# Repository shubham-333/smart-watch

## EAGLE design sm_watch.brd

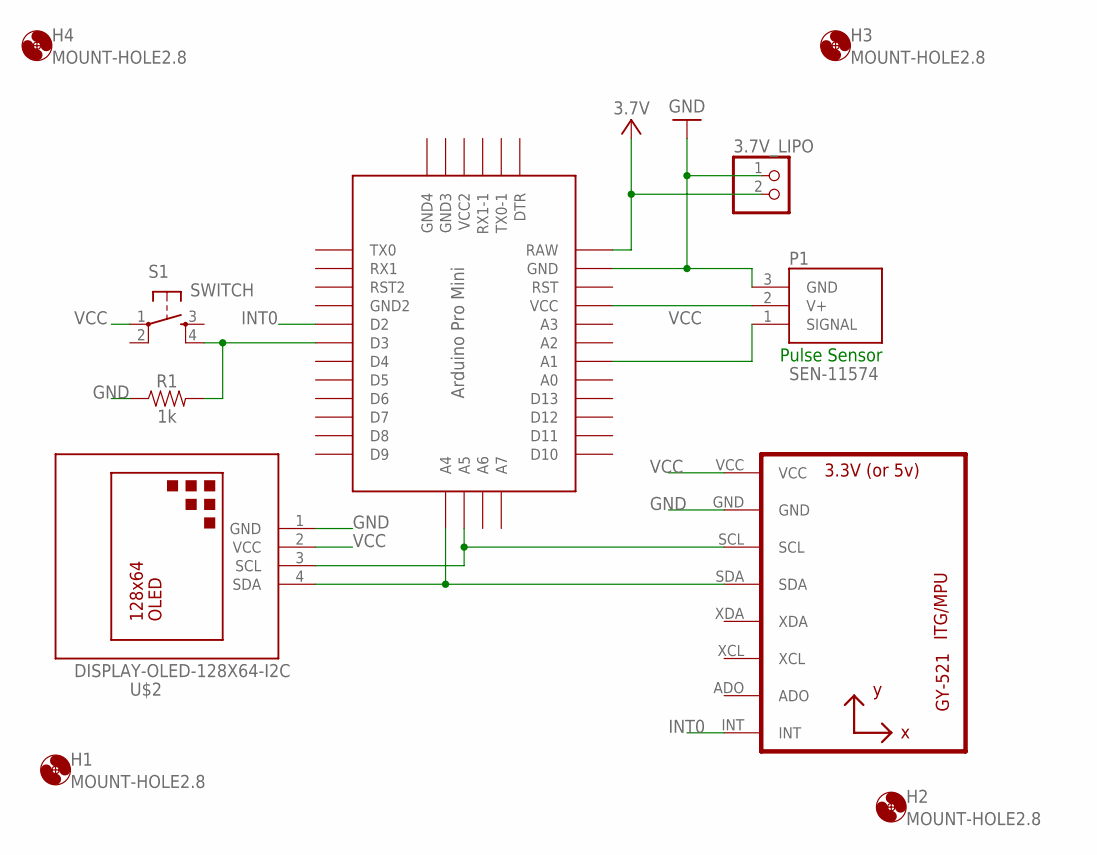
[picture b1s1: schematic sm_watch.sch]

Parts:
3.7V_LIPO: PINHD-1X2/90; 1X02/90
H1, H2, H3, H4: MOUNT-HOLE2.8; 2,8
P1: SEN-11574; XDCR_SEN-11574
R1: 1k; 0402-TIGHT
S1: SWITCH; DTS-6
U1: GY-521MPU6050; GY-521
U$1: PRO-MINI
U$2: DISPLAY-OLED-128X64-I2C

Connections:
+3V3: 3.7V_LIPO.2, U$1.RAW
GND: 3.7V_LIPO.1, P1.3 (GND), R1.1, U1.GND, U$1.GND, U$2.1 (GND)
INT0: U1.INT, U$1.D2
INT1: R1.2, S1.4, U$1.D3
unnamed: U1.SDA, U$1.A4, U$2.4 (SDA)
unnamed: U1.SCL, U$1.A5, U$2.3 (SCL)
unnamed: P1.1 (SIGNAL), U$1.A1
VCC: P1.2 (V+), S1.1, U1.VCC, U$1.VCC, U$2.2 (VCC)

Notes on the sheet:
Pulse Sensor

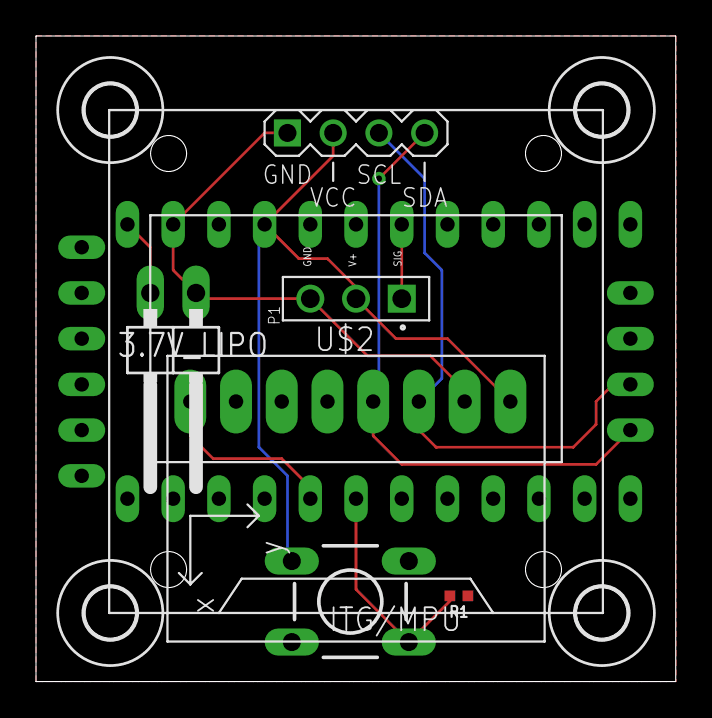
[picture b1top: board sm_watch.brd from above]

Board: 2 copper layers, 35.5 x 35.9 mm, 11 parts (0 on the bottom side), 8 nets.

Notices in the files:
parts and their libraries:
diy-modules: Released under the Creative Commons Attribution 4.0 International License: http://creativecommons.org/licenses/by/4.0
SparkFun-Resistors: Licensing: Creative Commons ShareAlike 4.0 International - https://creativecommons.org/licenses/by-sa/4.0
